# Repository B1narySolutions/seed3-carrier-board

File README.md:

# seed3-carrier

KiCad carrier board for the Daisy Seed, part of a capstone project: a portable touchscreen practice guitar amp.
The firmware is in [realtime-nam-seed3](https://github.com/B1narySolutions/realtime-nam-seed3).

## Layout

- `rev1/`: the board sent to fabrication on 2026-09-15 (also tagged `rev1`). Keep it unchanged while it is being tested. Manufacturing files are in `rev1/fabrication/`.
- `rev2/`: the next revision. The schematic starts as a copy of rev 1. There is no PCB file yet: rev 2 gets a full re-layout on a 4-layer stackup, starting from a new board in KiCad. Changes from rev 1 are listed in [`rev2/CHANGES.md`](rev2/CHANGES.md).
- `Seed3_Carrier.pretty/` and `seed3-carrier.kicad_sym`: footprint and symbol libraries shared by both revisions.
- `3dmodels/`: simplified STEP placeholder models for parts without a vendor 3D model (pots, jacks, Daisy Seed), generated by `make_placeholders.py`.
- `mechanical/`: STEP export of the rev 1 board assembly, for enclosure design.
- `TEST_PLAN.md`: post-assembly bring-up and acceptance tests for rev 1.
- [`studies/`](studies/): analysis of the board's behaviour (scripts, figures, write-ups). Current studies cover rev 1.

Open `rev1/seed3-carrier.kicad_pro` or `rev2/seed3-carrier.kicad_pro` in KiCad 10.

## Project documentation

Documentation lives alongside the work: hardware docs (board measurements, test plans, the rev 2 change list) in
this repository, firmware docs in [realtime-nam-seed3](https://github.com/B1narySolutions/realtime-nam-seed3).

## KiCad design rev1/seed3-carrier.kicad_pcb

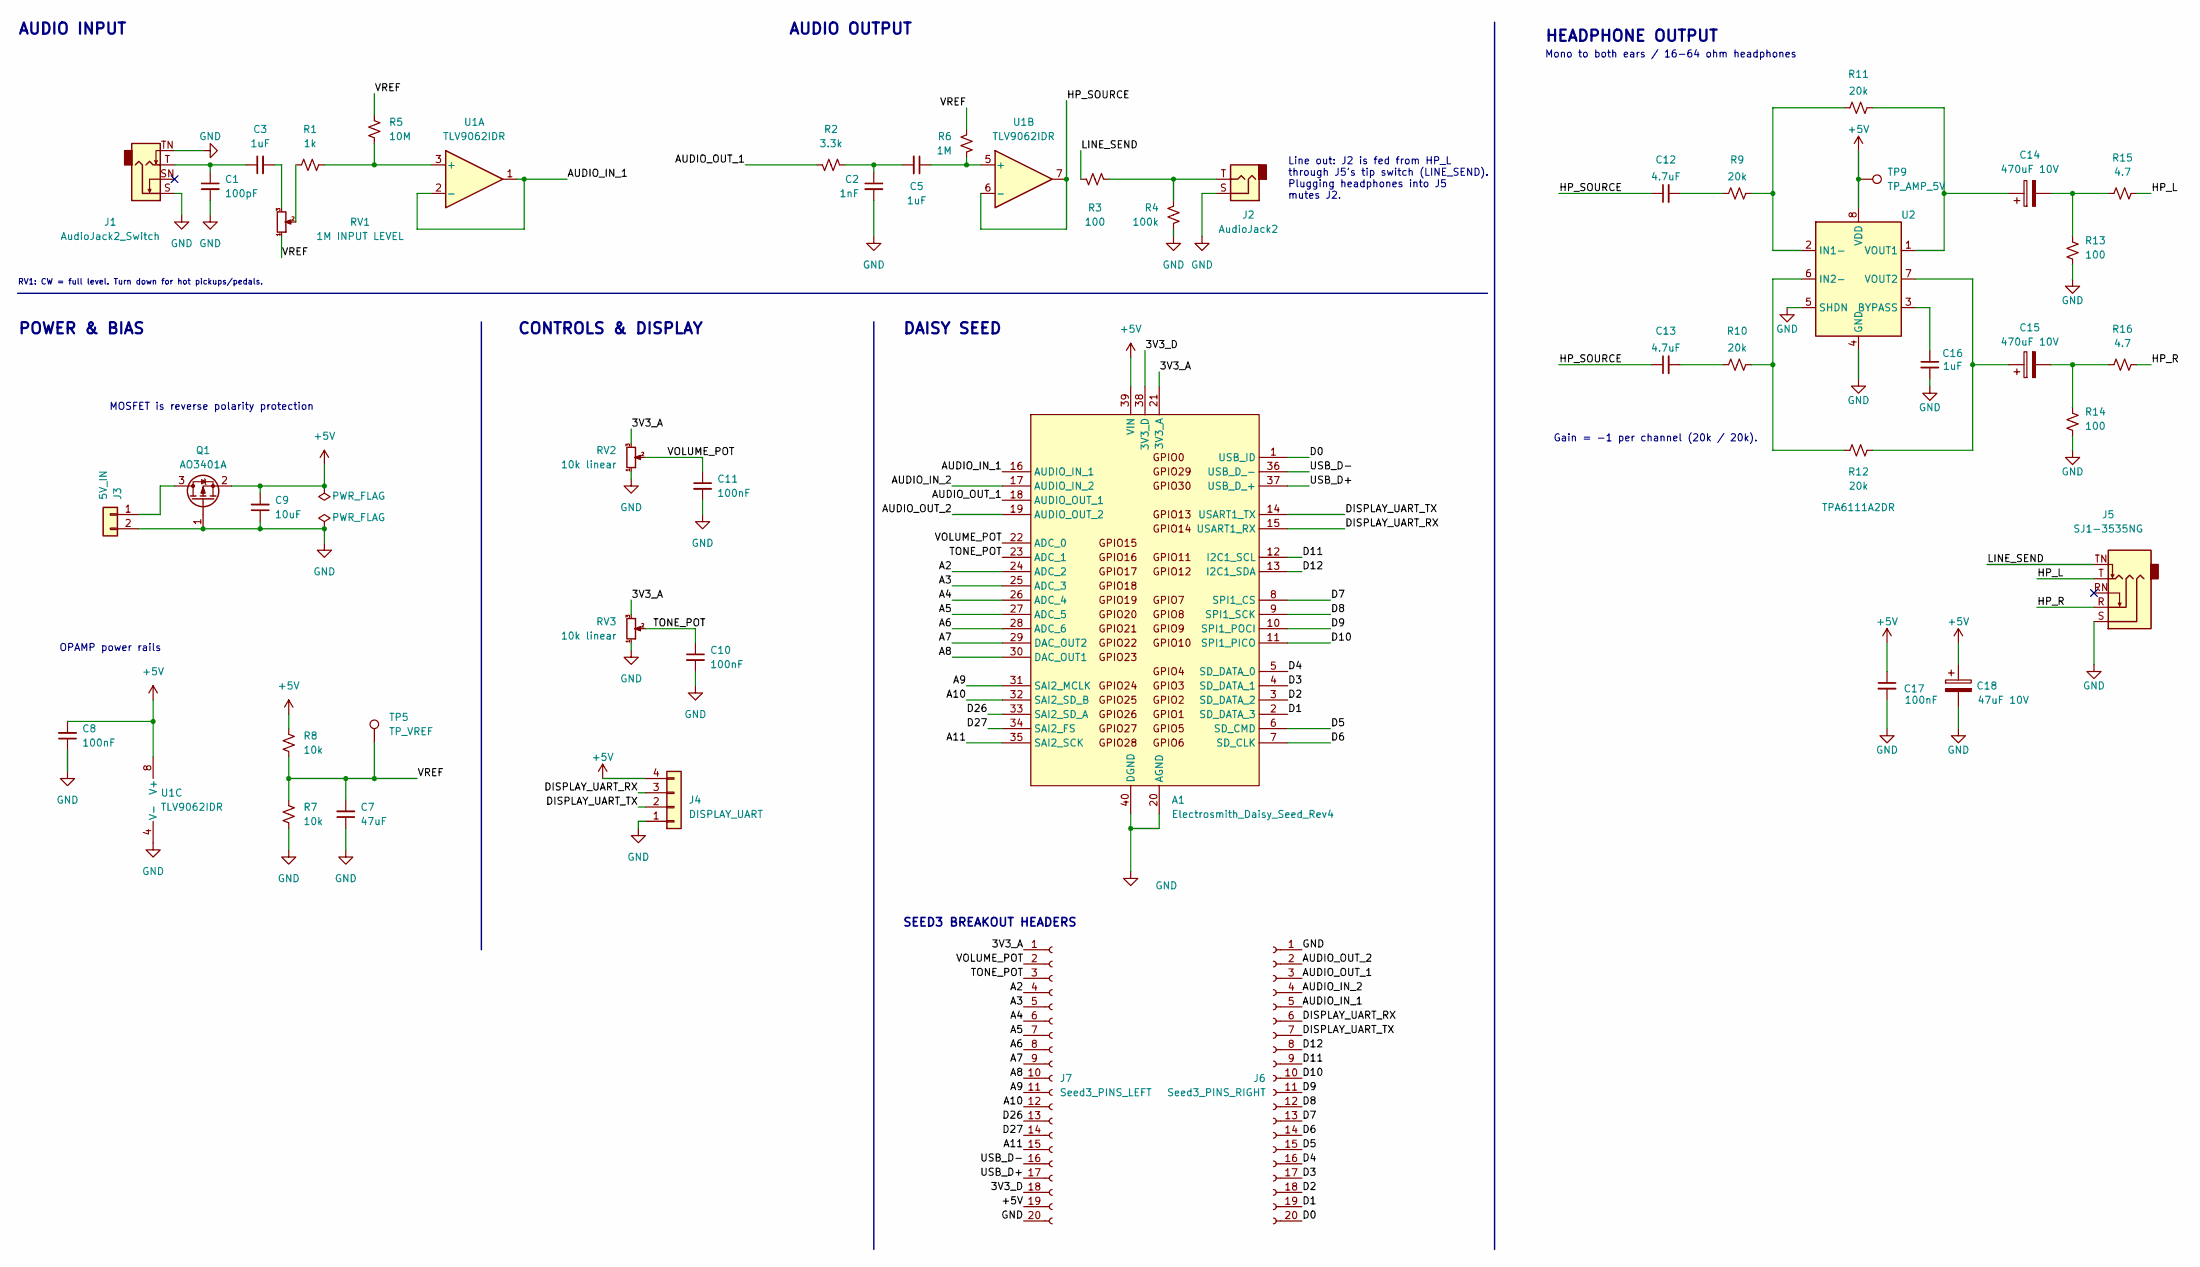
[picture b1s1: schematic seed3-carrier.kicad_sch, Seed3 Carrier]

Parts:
A1: Electrosmith_Daisy_Seed_Rev4; Electrosmith_Daisy_Seed
C1: 100pF; C_1206_3216Metric_Pad1.33x1.80mm_HandSolder
C2: 1nF; C_1206_3216Metric_Pad1.33x1.80mm_HandSolder
C3, C5, C16: 1uF; C_1206_3216Metric_Pad1.33x1.80mm_HandSolder
C7: 47uF; C_1210_3225Metric_Pad1.33x2.70mm_HandSolder
C8, C10, C11, C17: 100nF; C_1206_3216Metric_Pad1.33x1.80mm_HandSolder
C9: 10uF; C_1206_3216Metric_Pad1.33x1.80mm_HandSolder
C12, C13: 4.7uF; C_1210_3225Metric_Pad1.33x2.70mm_HandSolder; MPN GRM32ER71H475KA88L
C14, C15: 470uF 10V; CP_Radial_D8.0mm_P3.50mm
C18: 47uF 10V; CP_Radial_D5.0mm_P2.00mm
J1: AudioJack2_Switch; Jack_6.35mm_Neutrik_NRJ4HF_Horizontal
J2: AudioJack2; Jack_6.35mm_Neutrik_NRJ4HF_Horizontal
J3: 5V_IN; PinHeader_1x02_P2.54mm_Vertical
J4: DISPLAY_UART; PinHeader_1x04_P2.54mm_Vertical
J5: SJ1-3535NG; Jack_3.5mm_CUI_SJ1-3535NG_Horizontal
J6: Seed3_PINS_RIGHT; PinSocket_1x20_P2.54mm_Vertical
J7: Seed3_PINS_LEFT; PinSocket_1x20_P2.54mm_Vertical
Q1: AO3401A; SOT-23
R1: 1k; R_1206_3216Metric_Pad1.30x1.75mm_HandSolder
R2: 3.3k; R_1206_3216Metric_Pad1.30x1.75mm_HandSolder
R3, R13, R14: 100; R_1206_3216Metric_Pad1.30x1.75mm_HandSolder
R4: 100k; R_1206_3216Metric_Pad1.30x1.75mm_HandSolder
R5: 10M; R_1206_3216Metric_Pad1.30x1.75mm_HandSolder
R6: 1M; R_1206_3216Metric_Pad1.30x1.75mm_HandSolder
R7, R8: 10k; R_1206_3216Metric_Pad1.30x1.75mm_HandSolder
R9, R10, R11, R12: 20k; R_1206_3216Metric_Pad1.30x1.75mm_HandSolder
R15, R16: 4.7; R_1206_3216Metric_Pad1.30x1.75mm_HandSolder
RV1: 1M INPUT LEVEL; Potentiometer_Bourns_PTV09A-4_Single_Vertical_3mmMount; MPN PTV09A-4020F-B105
RV2, RV3: 10k linear; Potentiometer_Bourns_PTV09A-4_Single_Vertical_3mmMount; MPN PTV09A-4020F-B103
TP5: TP_VREF; TestPoint_Pad_D2.0mm
TP9: TP_AMP_5V; TestPoint_Pad_D2.0mm
U1: TLV9062IDR; SOIC-8_3.9x4.9mm_P1.27mm
U2: TPA6111A2DR; SOIC-8_3.9x4.9mm_P1.27mm

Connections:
+5V: A1.39 (VIN), C8.2, C9.2, C17.1, C18.1, J4.4, J7.19, Q1.2 (S), R8.1, TP9.1 (1_1), U1.8 (V+), U2.8 (VDD)
/3V3_A: A1.21 (3V3_A), J7.1, RV2.3, RV3.3
/3V3_D: A1.38 (3V3_D), J7.18
/A2: A1.24 (ADC_2), J7.4
/A3: A1.25 (ADC_3), J7.5
/A4: A1.26 (ADC_4), J7.6
/A5: A1.27 (ADC_5), J7.7
/A6: A1.28 (ADC_6), J7.8
/A7: A1.29 (DAC_OUT2), J7.9
/A8: A1.30 (DAC_OUT1), J7.10
/A9: A1.31 (SAI2_MCLK), J7.11
/A10: A1.32 (SAI2_SD_B), J7.12
/A11: A1.35 (SAI2_SCK), J7.15
/AUDIO_IN_1: A1.16 (AUDIO_IN_1), J6.5, U1.1, U1.2 (-)
/AUDIO_IN_2: A1.17 (AUDIO_IN_2), J6.4
/AUDIO_OUT_1: A1.18 (AUDIO_OUT_1), J6.3, R2.2
/AUDIO_OUT_2: A1.19 (AUDIO_OUT_2), J6.2
/D0: A1.1 (USB_ID), J6.20
/D1: A1.2 (SD_DATA_3), J6.19
/D2: A1.3 (SD_DATA_2), J6.18
/D3: A1.4 (SD_DATA_1), J6.17
/D4: A1.5 (SD_DATA_0), J6.16
/D5: A1.6 (SD_CMD), J6.15
/D6: A1.7 (SD_CLK), J6.14
/D7: A1.8 (SPI1_CS), J6.13
/D8: A1.9 (SPI1_SCK), J6.12
/D9: A1.10 (SPI1_POCI), J6.11
/D10: A1.11 (SPI1_PICO), J6.10
/D11: A1.12 (I2C1_SCL), J6.9
/D12: A1.13 (I2C1_SDA), J6.8
/D26: A1.33 (SAI2_SD_A), J7.13
/D27: A1.34 (SAI2_FS), J7.14
/DISPLAY_UART_RX: A1.15 (USART1_RX), J4.3, J6.6
/DISPLAY_UART_TX: A1.14 (USART1_TX), J4.2, J6.7
/HP_L: J5.T, R15.2
/HP_R: J5.R, R16.2
/HP_SOURCE: C12.1, C13.1, U1.6 (-), U1.7
/LINE_SEND: J5.TN, R3.2
/TONE_POT: A1.23 (ADC_1), C10.1, J7.3, RV3.2
/USB_D+: A1.37 (USB_D_+), J7.17
/USB_D-: A1.36 (USB_D_-), J7.16
/VOLUME_POT: A1.22 (ADC_0), C11.1, J7.2, RV2.2
/VREF: C7.2, R5.1, R6.1, R7.1, R8.2, RV1.1, TP5.1 (1_1)
GND: A1.20 (AGND), A1.40 (DGND), C1.2, C2.2, C7.1, C8.1, C9.1, C10.2, C11.2, C16.2, C17.2, C18.2, J1.S, J1.TN, J2.S, J3.2, J4.1, J5.S, J6.1, J7.20, Q1.1 (G), R4.1, R7.2, R13.2, R14.2, RV2.1, RV3.1, U1.4 (V-), U2.4 (GND), U2.5 (SHDN)
unnamed: C1.1, C3.1, J1.T
unnamed: C2.1, C5.2, R2.1
unnamed: C3.2, RV1.3
unnamed: C12.2, R9.1
unnamed: C13.2, R10.1
unnamed: C14.2, R13.1, R15.1
unnamed: C15.2, R14.1, R16.1
unnamed: J2.T, R3.1, R4.2
unnamed: J3.1, Q1.3 (D)
unnamed: R1.1, RV1.2
unnamed: R1.2, R5.2, U1.3 (+)
unnamed: C5.1, R6.2, U1.5 (+)
unnamed: C16.1, U2.3 (BYPASS)
unnamed: R9.2, R11.1, U2.2 (IN1-)
unnamed: R10.2, R12.1, U2.6 (IN2-)
unnamed: C14.1, R11.2, U2.1 (VOUT1)
unnamed: C15.1, R12.2, U2.7 (VOUT2)

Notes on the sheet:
RV1: CW = full level. Turn down for hot pickups/pedals.
HEADPHONE OUTPUT
AUDIO OUTPUT
DAISY SEED
SEED3 BREAKOUT HEADERS
OPAMP power rails
AUDIO INPUT
MOSFET is reverse polarity protection
Mono to both ears / 16-64 ohm headphones
Gain = -1 per channel (20k / 20k).
CONTROLS & DISPLAY
POWER & BIAS
Line out: J2 is fed from HP_L through J5's tip switch (LINE_SEND). Plugging headphones into J5 mutes J2.

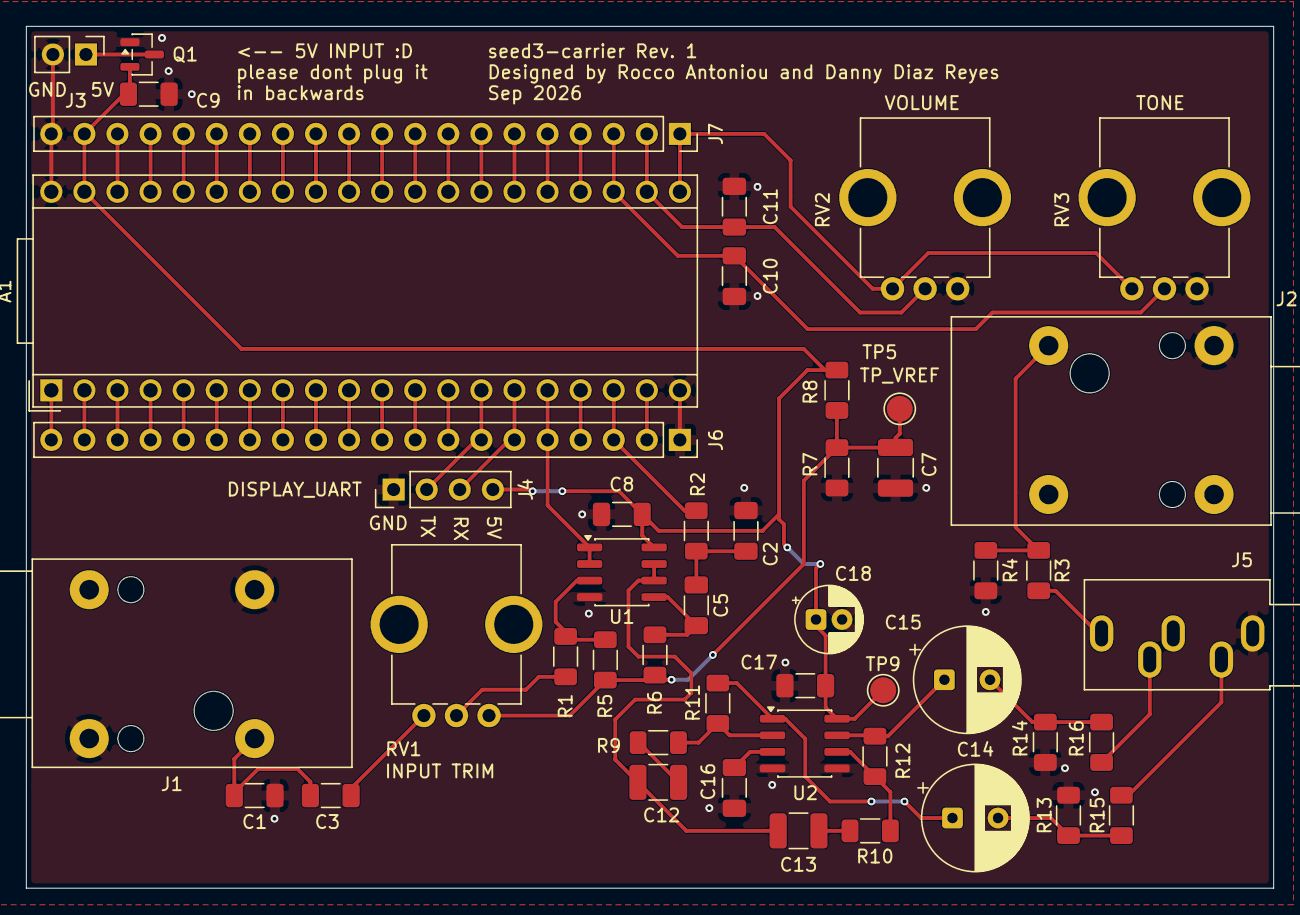
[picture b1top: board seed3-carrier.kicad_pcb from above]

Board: 2 copper layers, 95.8 x 66.2 mm, 48 parts (0 on the bottom side), 61 nets.

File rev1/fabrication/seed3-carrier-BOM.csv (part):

"References","Value","Quantity","Manufacturer","MPN","DigiKey Part Number","DigiKey URL","Footprint","DNP","Part Status","DigiKey Stock","Unit Price (qty 1)","Stock Checked","Purchase Quantity","Notes"
"A1","Electrosmith_Daisy_Seed_Rev4","1","Electrosmith","","","","Module:Electrosmith_Daisy_Seed","","","","","","0","Already purchased separately; use existing Daisy module. Legacy schematic symbol name retained; no DigiKey purchase."
"A1 sockets","Daisy socket 1x20","2","Sullins Connector Solutions","PPPC201LFBN-RC","S7053-ND","https://www.digikey.com/en/products/detail/sullins-connector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","","","Active","4,897","$1.26","2026-09-17","2","BOM-only line, not in schematic: two 1x20 female sockets soldered into A1's pin holes so the Daisy plugs in and can be swapped. Same part as J6/J7; buy four total. Keep this row when regenerating the BOM."
"C1","100pF","1","YAGEO","CC1206JRNPO9BN101","311-1161-1-ND","https://www.digikey.com/en/products/detail/yageo/CC1206JRNPO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","Capacitor_SMD:C_1206_3216Metric_Pad1.33x1.80mm_HandSolder","","Active","38,967","$0.30","2026-09-17","1","100pF; 50V; C0G/NP0; 5%; 1206; cut tape."
"C2","1nF","1","YAGEO","CC1206JRNPO9BN102","311-1163-1-ND","https://www.digikey.com/en/products/detail/yageo/CC1206JRNPO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","Capacitor_SMD:C_1206_3216Metric_Pad1.33x1.80mm_HandSolder","","Active","78,534","$0.29","2026-09-17","1","1nF; 50V; C0G/NP0; 5%; 1206; cut tape."
"C3,C5,C16","1uF","3","Samsung Electro-Mechanics","CL31B105KBHSNNE","1276-3093-1-ND","https://www.digikey.com/en/products/detail/samsung-electro-m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","Capacitor_SMD:C_1206_3216Metric_Pad1.33x1.80mm_HandSolder","","Active","249,465","$0.24","2026-09-17","3","1uF; 50V; X7R; 10%; 1206; cut tape."
"C7","47uF","1","Samsung Electro-Mechanics","CL32A476KOJNNNE","1276-3376-1-ND","https://www.digikey.com/en/products/detail/samsung-electro-m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","Capacitor_SMD:C_1210_3225Metric_Pad1.33x2.70mm_HandSolder","","Active","334,216","$0.87","2026-09-17","1","47uF; 16V; X5R; 10%; 1210; cut tape."
"C8,C10,C11,C17","100nF","4","Samsung Electro-Mechanics","CL31B104KBCNNNC","1276-1017-1-ND","https://www.digikey.com/en/products/detail/samsung-electro-m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","Capacitor_SMD:C_1206_3216Metric_Pad1.33x1.80mm_HandSolder","","Active","508,888","$0.14","2026-09-17","4","100nF; 50V; X7R; 10%; 1206; cut tape."
"C9","10uF","1","Taiyo Yuden","GMK316BJ106KL-T","587-2484-1-ND","https://www.digikey.com/en/products/detail/taiyo-yuden/GMK31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","Capacitor_SMD:C_1206_3216Metric_Pad1.33x1.80mm_HandSolder","","Not For New Designs","287,591","$0.37","2026-09-17","1","10uF; 35V; X5R; 10%; 1206; cut tape. NRND, but listed stock available."
"C12,C13","4.7uF","2","Murata Electronics","GRM32ER71H475KA88L","490-1864-1-ND","https://www.digikey.com/en/products/detail/murata-electronic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","Capacitor_SMD:C_1210_3225Metric_Pad1.33x2.70mm_HandSolder","","Not For New Designs","829,796","$1.74","2026-09-17","2","4.7uF; 50V; X7R; 10%; 1210; cut tape. Existing selected part retained; NRND."
"C14,C15","470uF 10V","2","Nichicon","UVR1C471MPD1TD","UVR1C471MPDDCT-ND","https://www.digikey.com/en/products/detail/nichicon/UVR1C471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","Capacitor_THT:CP_Radial_D8.0mm_P3.50mm","","Active","58,780","$0.39","2026-09-17","2","470uF; 16V (exceeds 10V requirement); 8mm diameter; 3.5mm pitch; 13mm max height; cut tape."
"C18","47uF 10V","1","Panasonic Industry","EEU-FC1C470","P11196-ND","https://www.digikey.com/en/products/detail/panasonic-electro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","Capacitor_THT:CP_Radial_D5.0mm_P2.00mm","","Active","14,309","$0.39","2026-09-17","1","47uF; 16V (exceeds 10V requirement); 5mm diameter; 2mm pitch; 12mm max height; bulk."
"J1","AudioJack2_Switch","1","Neutrik","NRJ4HF","6473-NRJ4HF-ND","https://www.digikey.com/en/products/detail/neutrik-americas-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","Connector_Audio:Jack_6.35mm_Neutrik_NRJ4HF_Horizontal","","Active","390","$1.20","2026-09-17","1","6.35mm audio jack; exact footprint model. J1 and J2 use the same part; buy two total."
"J2","AudioJack2","1","Neutrik","NRJ4HF","6473-NRJ4HF-ND","https://www.digikey.com/en/products/detail/neutrik-americas-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","Connector_Audio:Jack_6.35mm_Neutrik_NRJ4HF_Horizontal","","Active","390","$1.20","2026-09-17","1","6.35mm audio jack; exact footprint model. J1 and J2 use the same part; buy two total."
"J3","5V_IN","1","Amphenol ICC (FCI)","68000-102HLF","609-3500-ND","https://www.digikey.com/en/products/detail/amphenol-cs-fci/6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","Connector_PinHeader_2.54mm:PinHeader_1x02_P2.54mm_Vertical","","Active","102,059","$0.24","2026-09-17","1","1x2 straight male header; 2.54mm pitch; bulk."
"J4","DISPLAY_UART","1","Amphenol ICC (FCI)","68000-104HLF","609-3248-ND","https://www.digikey.com/en/products/detail/amphenol-icc-fci/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","Connector_PinHeader_2.54mm:PinHeader_1x04_P2.54mm_Vertical","","Active","12,245","$0.44","2026-09-17","1","1x4 straight male header; 2.54mm pitch; bulk."
"J5","SJ1-3535NG","1","Same Sky (formerly CUI Devices)","SJ1-3535NG","CP1-3535NG-ND","https://www.digikey.com/en/products/detail/same-sky-formerly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","Connector_Audio:Jack_3.5mm_CUI_SJ1-3535NG_Horizontal","","Active","27,525","$1.62","2026-09-17","1","3.5mm stereo audio jack; exact footprint model."
"J6","Seed3_PINS_RIGHT","1","Sullins Connector Solutions","PPPC201LFBN-RC","S7053-ND","https://www.digikey.com/en/products/detail/sullins-connector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","Connector_PinSocket_2.54mm:PinSocket_1x20_P2.54mm_Vertical","","Active","4,897","$1.26","2026-09-17","1","1x20 straight female socket; 2.54mm pitch. J6, J7 and the two A1 Daisy sockets use the same part; buy four total."
"J7","Seed3_PINS_LEFT","1","Sullins Connector Solutions","PPPC201LFBN-RC","S7053-ND","https://www.digikey.com/en/products/detail/sullins-connector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","Connector_PinSocket_2.54mm:PinSocket_1x20_P2.54mm_Vertical","","Active","4,897","$1.26","2026-09-17","1","1x20 straight female socket; 2.54mm pitch. J6, J7 and the two A1 Daisy sockets use the same part; buy four total."
"Q1","AO3401A","1","Alpha & Omega Semiconductor","AO3401A","785-1001-1-ND","https://www.digikey.com/en/products/detail/alpha-omega-semic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","Package_TO_SOT_SMD:SOT-23","","Active","420,499","$0.52","2026-09-17","1","P-channel MOSFET; SOT-23; cut tape."
"R1","1k","1","YAGEO","RC1206FR-071KL","311-1.00KFRCT-ND","https://www.digikey.com/en/products/detail/yageo/RC1206FR-07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","Resistor_SMD:R_1206_3216Metric_Pad1.30x1.75mm_HandSolder","","Active","820,500","$0.10","2026-09-17","1","1206; 1%; 0.25W; cut tape."
"R2","3.3k","1","YAGEO","RC1206FR-073K3L","311-3.30KFRCT-ND","https://www.digikey.com/en/products/detail/yageo/RC1206FR-07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","Resistor_SMD:R_1206_3216Metric_Pad1.30x1.75mm_HandSolder","","Active","5,978","$0.10","2026-09-17","1","1206; 1%; 0.25W; cut tape."
"R3,R13,R14","100","3","YAGEO","RC1206FR-07100RL","311-100FRCT-ND","https://www.digikey.com/en/products/detail/yageo/RC1206FR-07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","Resistor_SMD:R_1206_3216Metric_Pad1.30x1.75mm_HandSolder","","Active","468,264","$0.10","2026-09-17","3","1206; 1%; 0.25W; cut tape."
"R4","100k","1","YAGEO","RC1206FR-07100KL","311-100KFRCT-ND","https://www.digikey.com/en/products/detail/yageo/RC1206FR-07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","Resistor_SMD:R_1206_3216Metric_Pad1.30x1.75mm_HandSolder","","Active","587,782","$0.10","2026-09-17","1","1206; 1%; 0.25W; cut tape."
"R5","10M","1","YAGEO","RC1206FR-0710ML","311-10.0MFRCT-ND","https://www.digikey.com/en/products/detail/yageo/RC1206FR-07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","Resistor_SMD:R_1206_3216Metric_Pad1.30x1.75mm_HandSolder","","Active","474","$0.10","2026-09-17","1","1206; 1%; 0.25W; cut tape."
"R6","1M","1","YAGEO","RC1206FR-071ML","311-1.00MFRCT-ND","https://www.digikey.com/en/products/detail/yageo/RC1206FR-07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","Resistor_SMD:R_1206_3216Metric_Pad1.30x1.75mm_HandSolder","","Active","217,170","$0.10","2026-09-17","1","1206; 1%; 0.25W; cut tape."
"R7,R8","10k","2","YAGEO","RC1206FR-0710KL","311-10.0KFRCT-ND","https://www.digikey.com/en/products/detail/yageo/RC1206FR-07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","Resistor_SMD:R_1206_3216Metric_Pad1.30x1.75mm_HandSolder","","Active","1,959,798","$0.11","2026-09-17","2","1206; 1%; 0.25W; cut tape."
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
